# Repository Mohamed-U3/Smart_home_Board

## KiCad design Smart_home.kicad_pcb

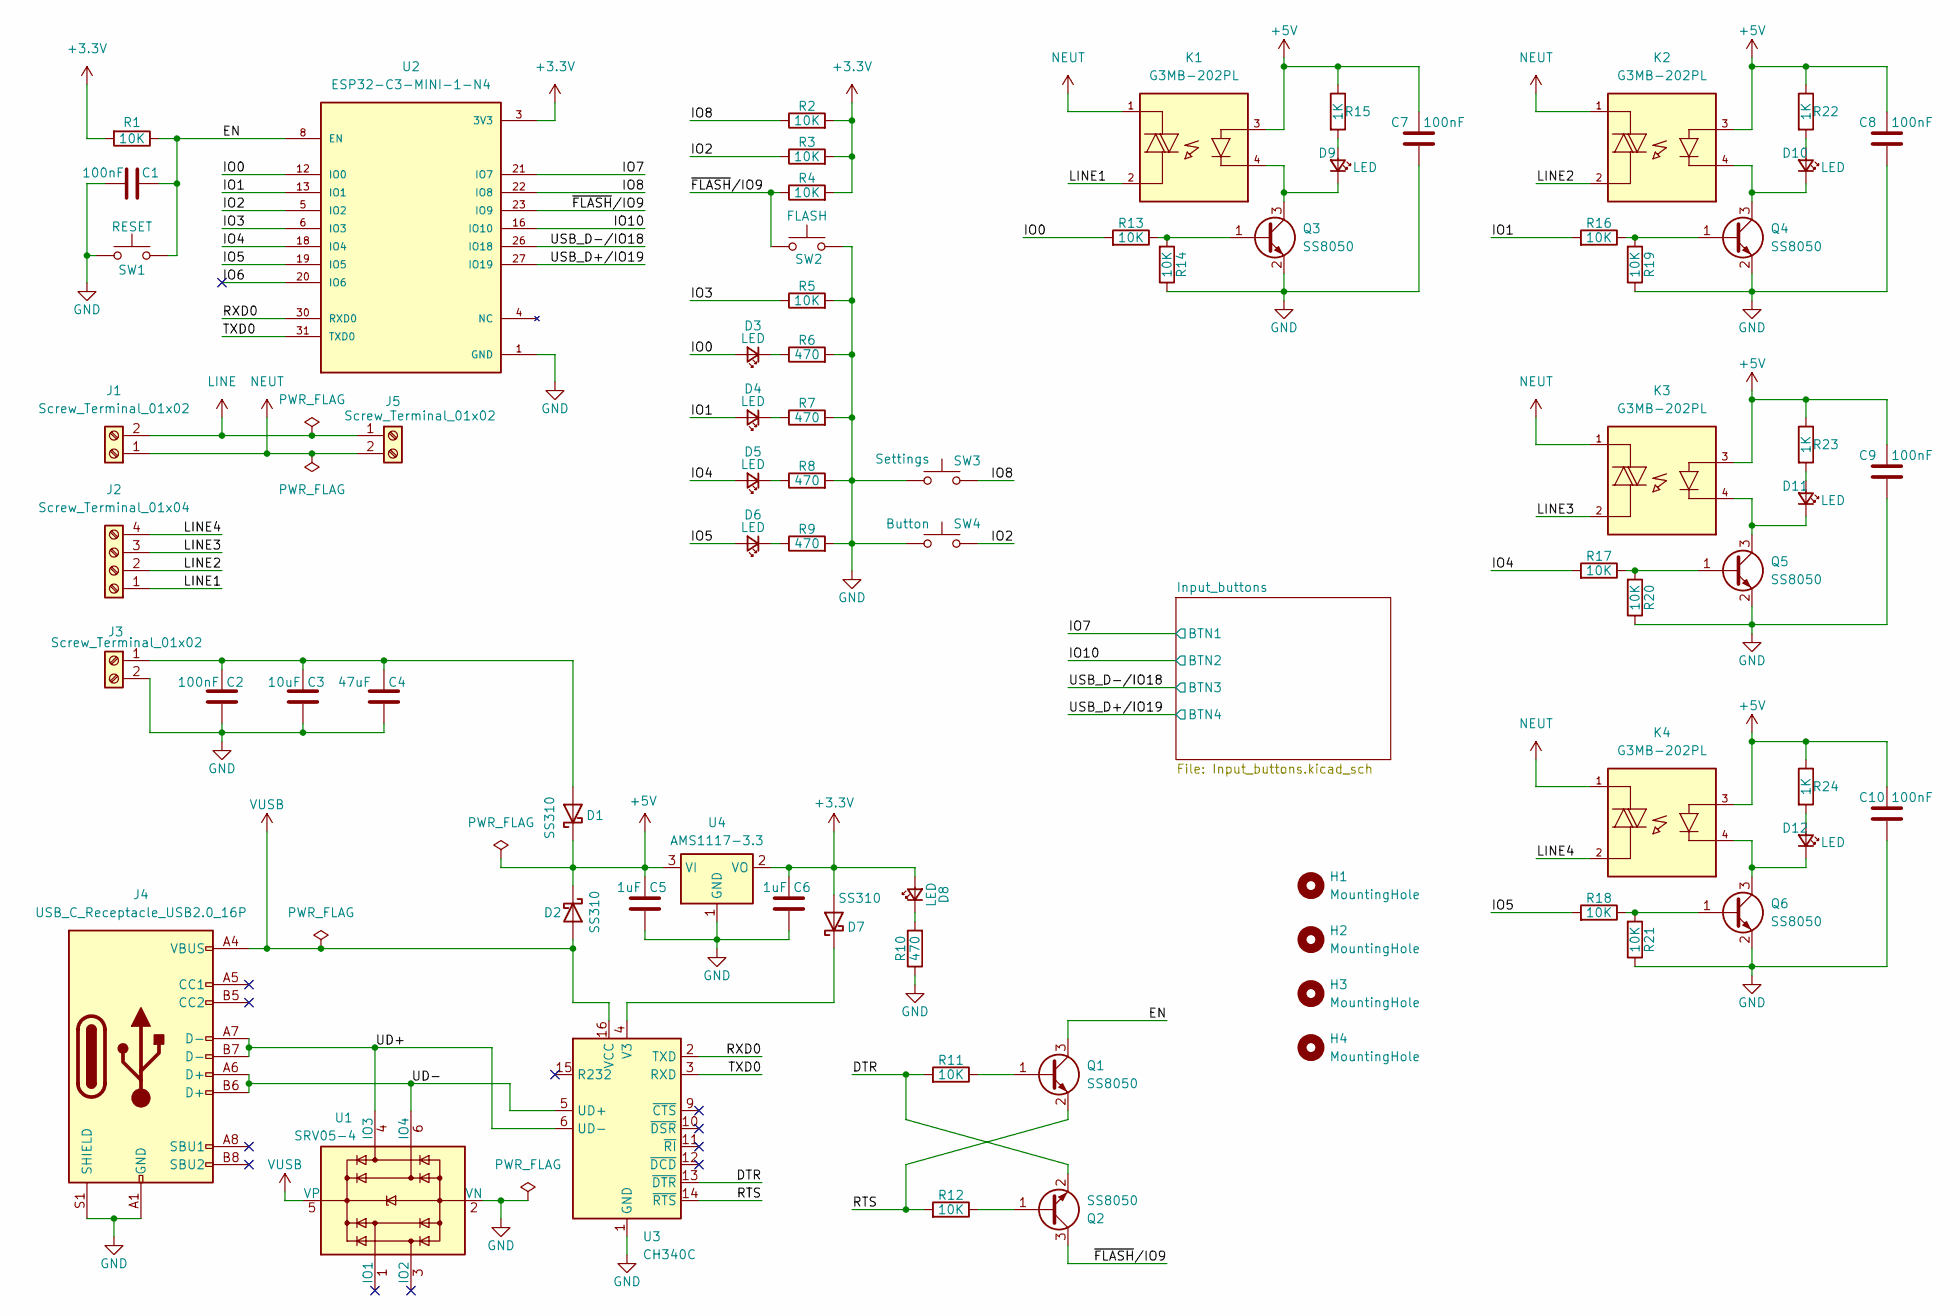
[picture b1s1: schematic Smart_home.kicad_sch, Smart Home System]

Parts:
C1, C2, C7, C8, C9, C10: 100nF; C_0603_1608Metric_Pad1.08x0.95mm_HandSolder
C3: 10uF; C_0603_1608Metric_Pad1.08x0.95mm_HandSolder
C4: 47uF; C_1206_3216Metric_Pad1.33x1.80mm_HandSolder
C5, C6: 1uF; C_0603_1608Metric_Pad1.08x0.95mm_HandSolder
D1, D2, D7: SS310; D_SMA
D3, D4, D5, D6, D8, D9, D10, D11, D12: LED; LED_0603_1608Metric
H1, H2, H3, H4: MountingHole; MountingHole_3.2mm_M3
J1: Screw_Terminal_01x02; TerminalBlock_Phoenix_MKDS-1,5-2-5.08_1x02_P5.08mm_Horizont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
J2: Screw_Terminal_01x04; TerminalBlock_Phoenix_MKDS-1,5-4-5.08_1x04_P5.08mm_Horizont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
J3, J5: Screw_Terminal_01x02; SolderWire-0.1sqmm_1x02_P3.6mm_D0.4mm_OD1mm_Relief
J4: USB_C_Receptacle_USB2.0_16P; USB_C_Receptacle_XKB_U262-16XN-4BVC11
K1, K2, K3, K4: G3MB-202PL; RELAY_G3MB-202PL; PARTREV 06/09
Q1, Q2, Q3, Q4, Q5, Q6: SS8050; SOT-23
R1, R2, R3, R4, R5, R11, R12, R13, R14, R16, R17, R18, R19, R20, R21: 10K; R_0805_2012Metric_Pad1.20x1.40mm_HandSolder
R6, R7, R8, R9, R10: 470; R_0805_2012Metric_Pad1.20x1.40mm_HandSolder
R15, R22, R23, R24: 1K; R_0805_2012Metric_Pad1.20x1.40mm_HandSolder
SW1: RESET; SW_SPST_PTS810
SW2: FLASH; SW_SPST_PTS810
SW3: Settings; SW_SPST_PTS810
SW4: Button; SW_SPST_PTS810
U1: SRV05-4; SOT-23-6
U2: ESP32-C3-MINI-1-N4; XCVR_ESP32-C3-MINI-1-N4; PARTREV v1.0
U3: CH340C; SOIC-16_3.9x9.9mm_P1.27mm
U4: AMS1117-3.3; SOT-89-3_Handsoldering

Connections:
+3.3V: C6.1, D7.2 (A), D8.2 (A), R1.2, R2.2, R3.2, R4.2, U2.3 (3V3), U4.2 (VO)
+5V: C5.1, C7.1, C8.1, C9.1, C10.1, D1.1 (K), D2.1 (K), K1.3, K2.3, K3.3, K4.3, R15.1, R22.1, R23.1, R24.1, U4.3 (VI); also elsewhere on the board
/DTR: Q2.2 (E), R11.2, U3.13 (~DTR)
/EN: C1.1, Q1.3 (C), R1.1, SW1.2, U2.8 (EN)
/IO0: D3.2 (A), R13.2, U2.12 (IO0)
/IO1: D4.2 (A), R16.2, U2.13 (IO1)
/IO2: R3.1, SW4.1, U2.5 (IO2)
/IO3: R5.1, U2.6 (IO3)
/IO4: D5.2 (A), R17.2, U2.18 (IO4)
/IO5: D6.2 (A), R18.2, U2.19 (IO5)
/IO6: U2.20 (IO6)
/IO7: U2.21 (IO7); also elsewhere on the board
/IO8: R2.1, SW3.1, U2.22 (IO8)
/IO10: U2.16 (IO10); also elsewhere on the board
/LINE1: J2.1, K1.2
/LINE2: J2.2, K2.2
/LINE3: J2.3, K3.2
/LINE4: J2.4, K4.2
/RTS: Q1.2 (E), R12.2, U3.14 (~RTS)
/RXD0: U2.30 (RXD0), U3.2 (TXD)
/TXD0: U2.31 (TXD0), U3.3 (RXD)
/UD+: J4.A7 (D-), J4.B7 (D-), U1.4 (IO3), U3.6 (UD-)
/UD-: J4.A6 (D+), J4.B6 (D+), U1.6 (IO4), U3.5 (UD+)
/USB_D+/IO19: U2.27 (IO19); also elsewhere on the board
/USB_D-/IO18: U2.26 (IO18); also elsewhere on the board
/~FLASH/IO9: Q2.3 (C), R4.1, SW2.1, U2.23 (IO9)
GND: C1.2, C2.2, C3.2, C4.2, C5.2, C6.2, C7.2, C8.2, C9.2, C10.2, J3.2, J4.A1 (GND), J4.A12 (GND), J4.B1 (GND), J4.B12 (GND), J4.S1 (SHIELD), Q3.2 (E), Q4.2 (E), Q5.2 (E), Q6.2 (E), R5.2, R6.2, R7.2, R8.2, R9.2, R10.1, R14.1, R19.1, R20.1, R21.1, SW1.1, SW2.2, SW3.2, SW4.2, U1.2 (VN), U2.1 (GND), U2.2 (GND), U2.11 (GND), U2.14 (GND), U2.36 (GND), U2.37 (GND), U2.38 (GND), U2.39 (GND), U2.40 (GND), U2.41 (GND), U2.42 (GND), U2.43 (GND), U2.44 (GND), U2.45 (GND), U2.46 (GND), U2.47 (GND), U2.48 (GND), U2.49_1 (GND), U2.49_2 (GND), U2.49_3 (GND), U2.49_4 (GND), U2.49_5 (GND), U2.49_6 (GND), U2.49_7 (GND), U2.49_8 (GND), U2.49_9 (GND), U2.50 (GND), U2.51 (GND), U2.52 (GND), U2.53 (GND), U3.1 (GND), U4.1 (GND); also elsewhere on the board
LINE: J1.2, J5.1
NEUT: J1.1, J5.2, K1.1, K2.1, K3.1, K4.1
unnamed: C2.1, C3.1, C4.1, D1.2 (A), J3.1
unnamed: D3.1 (K), R6.1
unnamed: D4.1 (K), R7.1
unnamed: D5.1 (K), R8.1
unnamed: D6.1 (K), R9.1
unnamed: D7.1 (K), U3.4 (V3)
unnamed: D8.1 (K), R10.2
unnamed: D9.2 (A), R15.2
unnamed: D9.1 (K), K1.4, Q3.3 (C)
unnamed: D10.2 (A), R22.2
unnamed: D10.1 (K), K2.4, Q4.3 (C)
unnamed: D11.2 (A), R23.2
unnamed: D11.1 (K), K3.4, Q5.3 (C)
unnamed: D12.2 (A), R24.2
unnamed: D12.1 (K), K4.4, Q6.3 (C)
unnamed: Q1.1 (B), R11.1
unnamed: Q2.1 (B), R12.1
unnamed: Q3.1 (B), R13.1, R14.2
unnamed: Q4.1 (B), R16.1, R19.2
unnamed: Q5.1 (B), R17.1, R20.2
unnamed: Q6.1 (B), R18.1, R21.2
VUSB: D2.2 (A), J4.A4 (VBUS), J4.A9 (VBUS), J4.B4 (VBUS), J4.B9 (VBUS), U1.5 (VP), U3.16 (VCC)

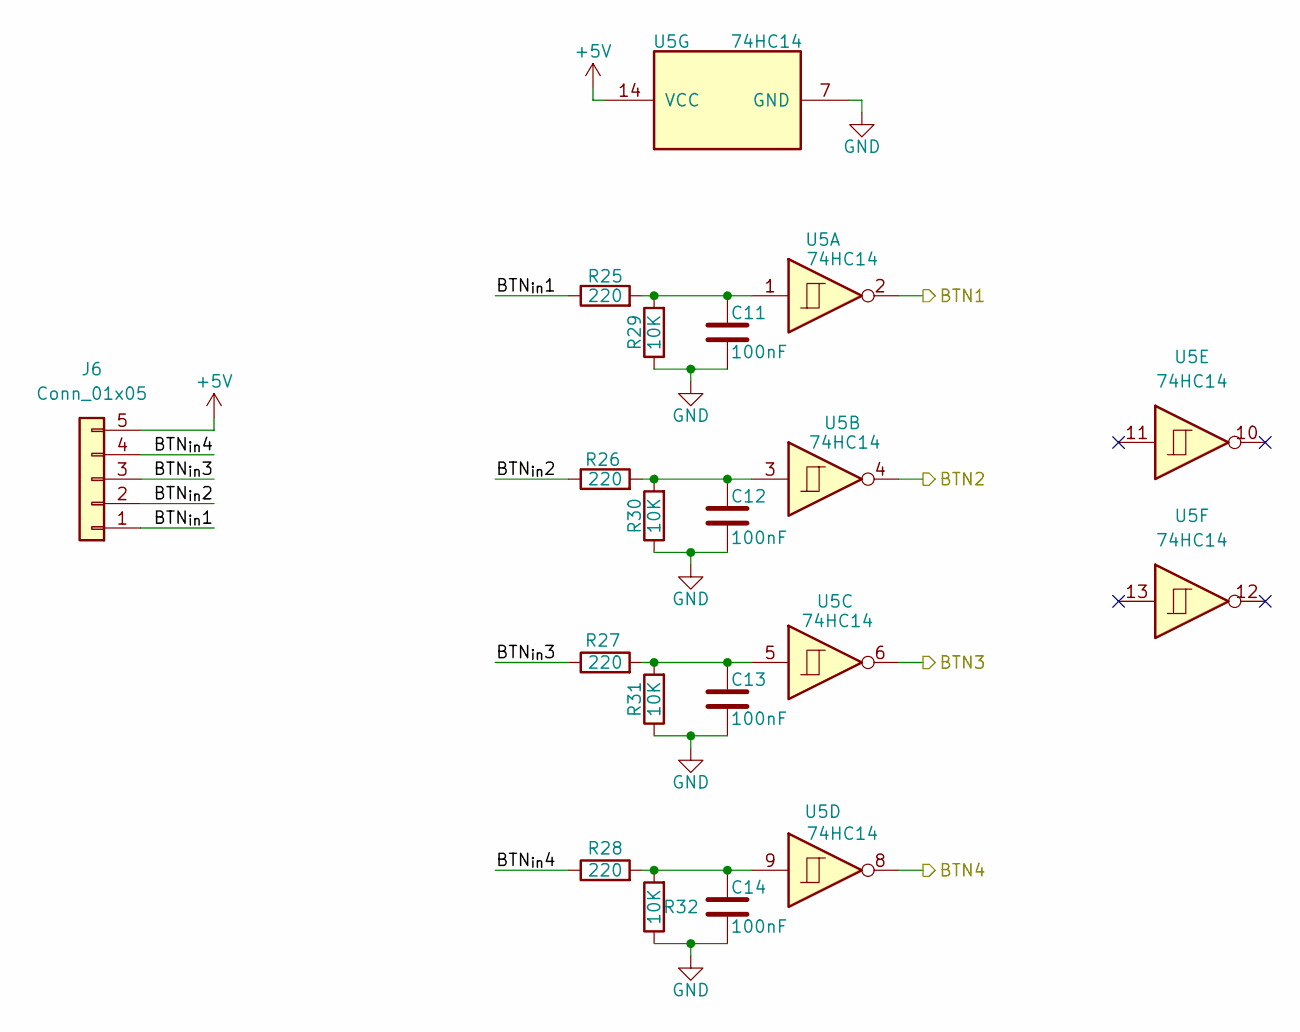
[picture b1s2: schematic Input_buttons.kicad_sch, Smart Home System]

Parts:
C11, C12, C13, C14: 100nF; C_0603_1608Metric_Pad1.08x0.95mm_HandSolder
J6: Conn_01x05; JST_XH_B5B-XH-A_1x05_P2.50mm_Vertical
R25, R26, R27, R28: 220; R_0603_1608Metric_Pad0.98x0.95mm_HandSolder
R29, R30, R31, R32: 10K; R_0805_2012Metric_Pad1.20x1.40mm_HandSolder
U5: 74HC14; SOIC-14_3.9x8.7mm_P1.27mm

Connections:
+5V: J6.5, U5.14 (VCC); also elsewhere on the board
/IO7: U5.2; also elsewhere on the board
/IO10: U5.4; also elsewhere on the board
/Input_buttons/BTN_{in}1: J6.1, R25.1
/Input_buttons/BTN_{in}2: J6.2, R26.1
/Input_buttons/BTN_{in}3: J6.3, R27.1
/Input_buttons/BTN_{in}4: J6.4, R28.1
/USB_D+/IO19: U5.8; also elsewhere on the board
/USB_D-/IO18: U5.6; also elsewhere on the board
GND: C11.2, C12.2, C13.2, C14.2, R29.1, R30.1, R31.1, R32.1, U5.7 (GND); also elsewhere on the board
unnamed: C11.1, R25.2, R29.2, U5.1
unnamed: C12.1, R26.2, R30.2, U5.3
unnamed: C13.1, R27.2, R31.2, U5.5
unnamed: C14.1, R28.2, R32.2, U5.9

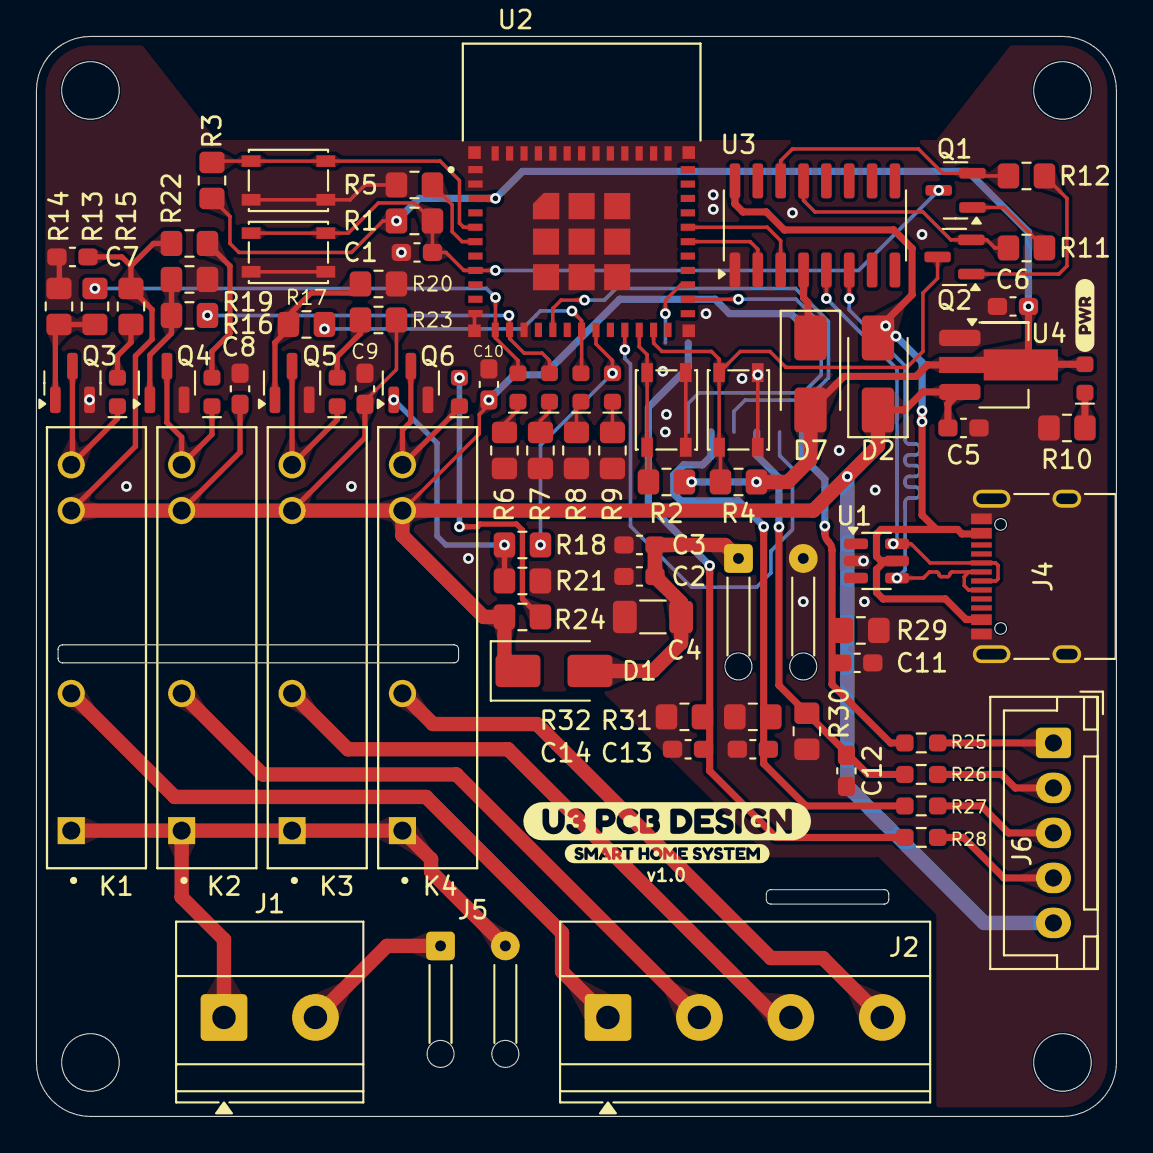
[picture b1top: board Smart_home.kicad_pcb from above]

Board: 2 copper layers, 60.0 x 60.0 mm, 90 parts (1 on the bottom side), 58 nets.

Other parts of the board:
kibuzzard-6A2A52E4: G***; kibuzzard-6A2A52E4
kibuzzard-6A2A5232: G***; kibuzzard-6A2A5232
kibuzzard-6A203CA8: G***; kibuzzard-6A203CA8

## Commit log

2026-06-03 first version.. almost finished
2026-06-11 Version v1.0 is ready for manufacturing.
2026-06-15 Final version of the production
